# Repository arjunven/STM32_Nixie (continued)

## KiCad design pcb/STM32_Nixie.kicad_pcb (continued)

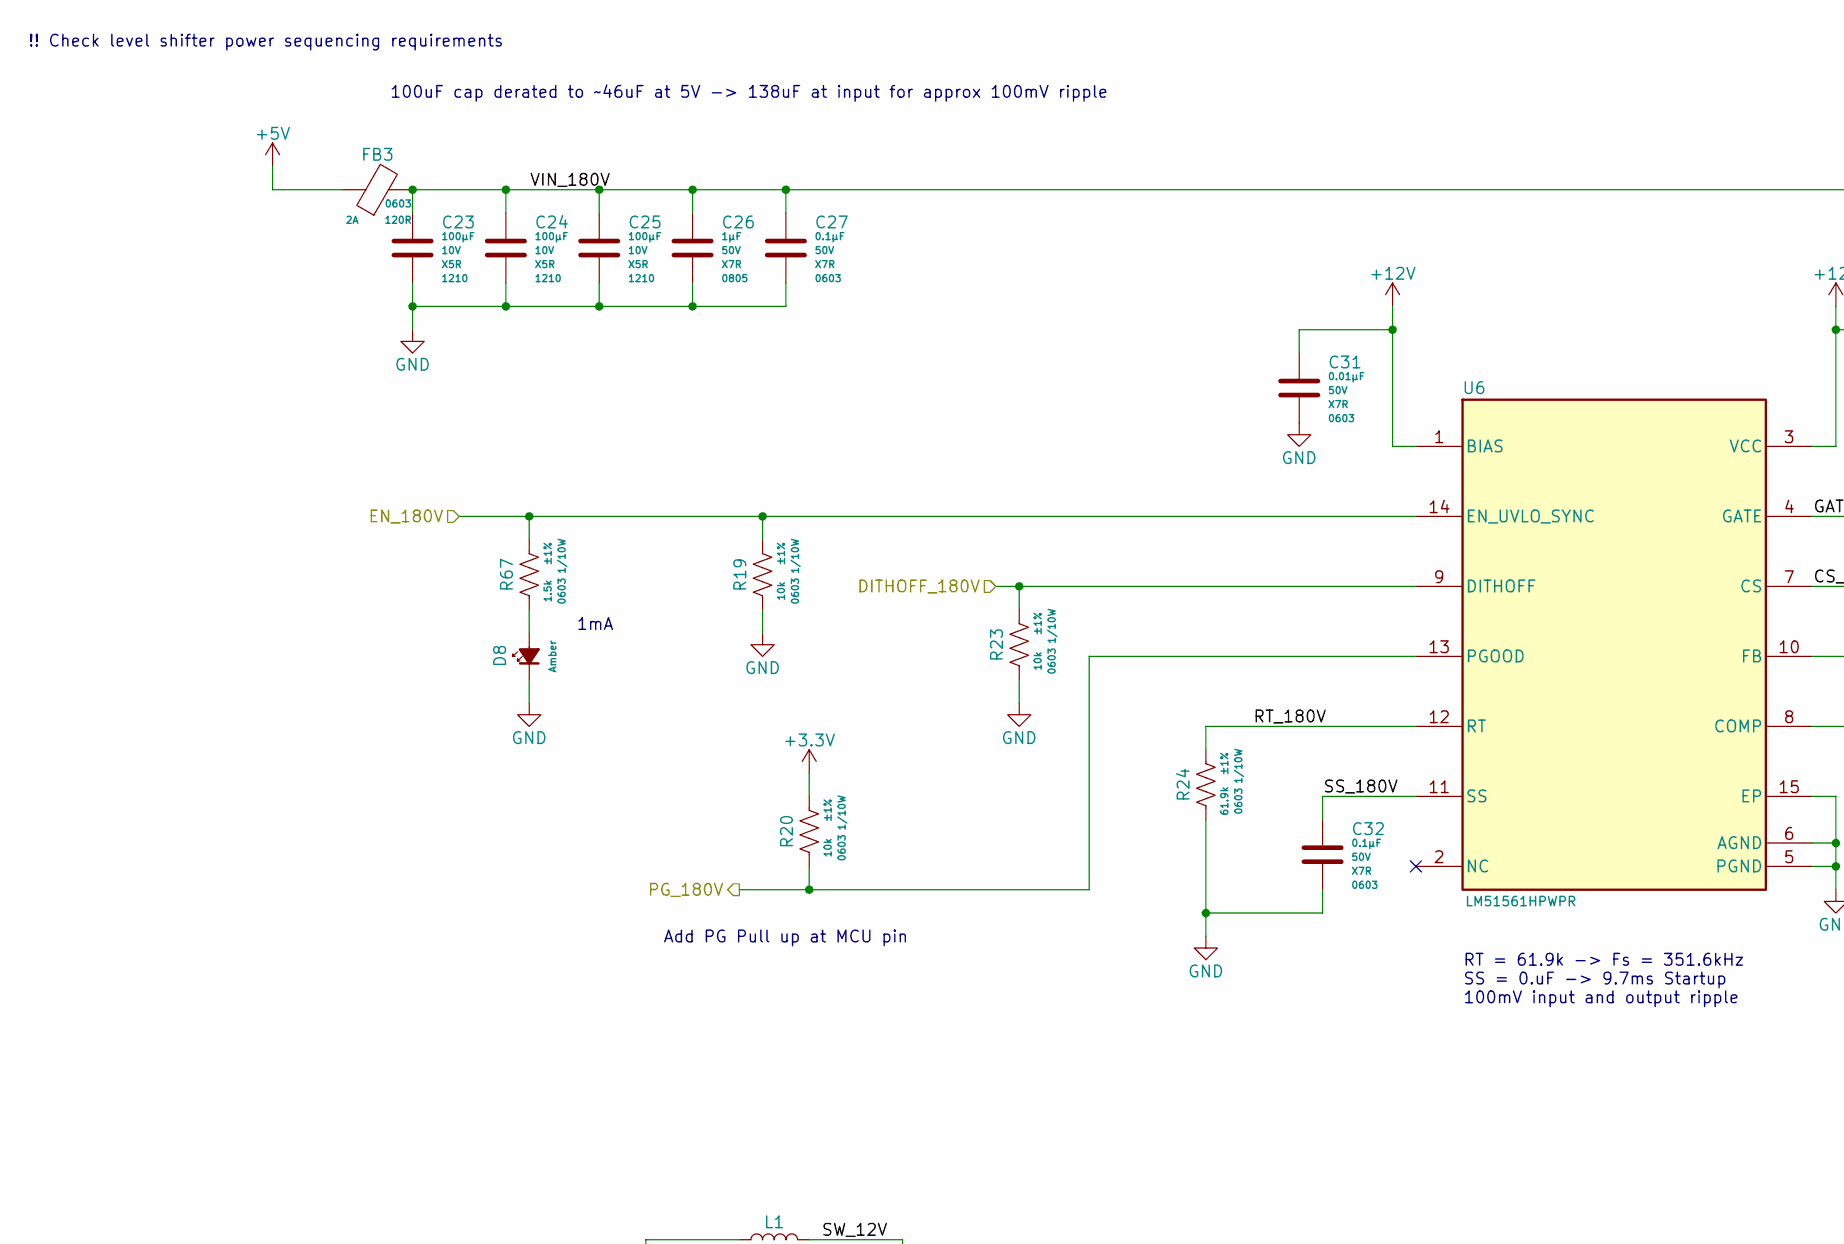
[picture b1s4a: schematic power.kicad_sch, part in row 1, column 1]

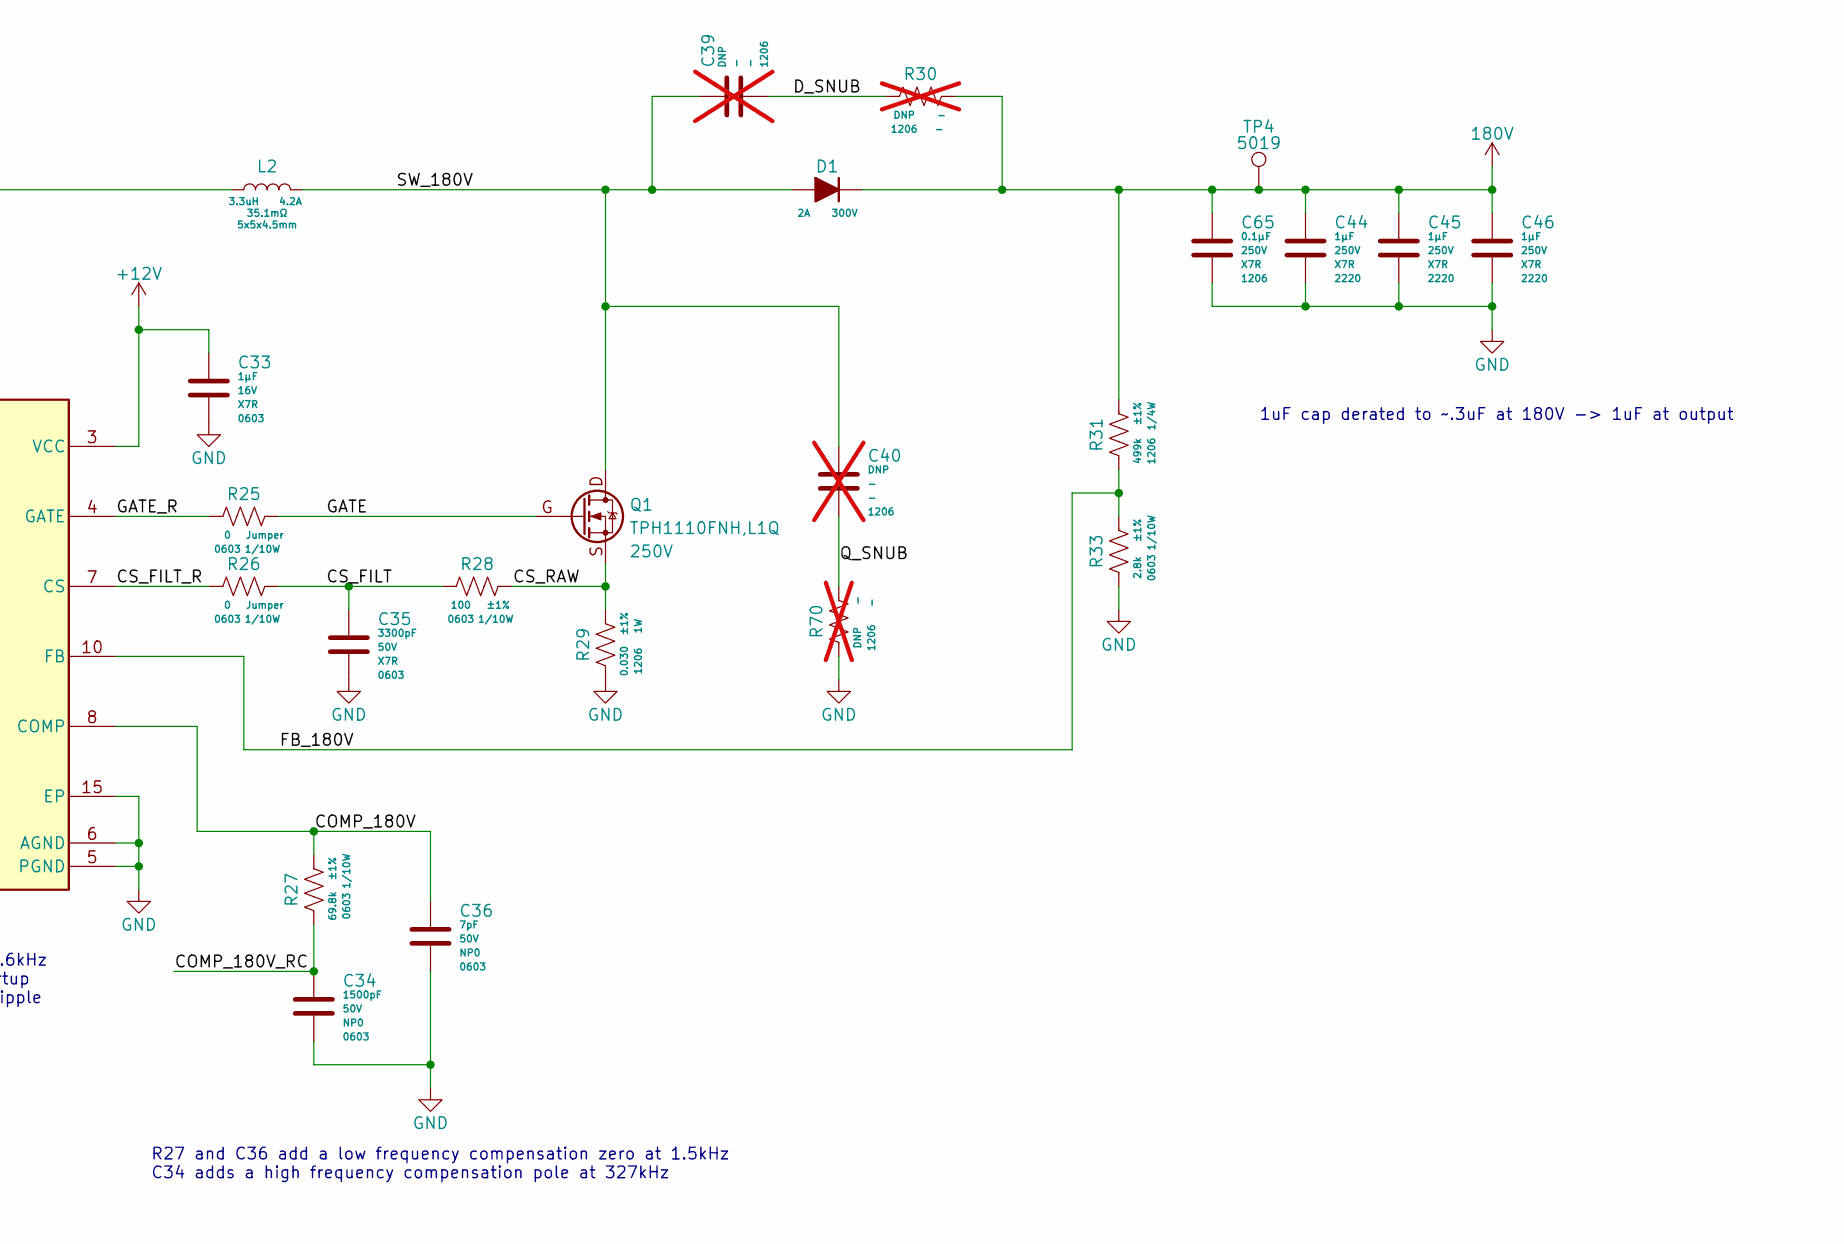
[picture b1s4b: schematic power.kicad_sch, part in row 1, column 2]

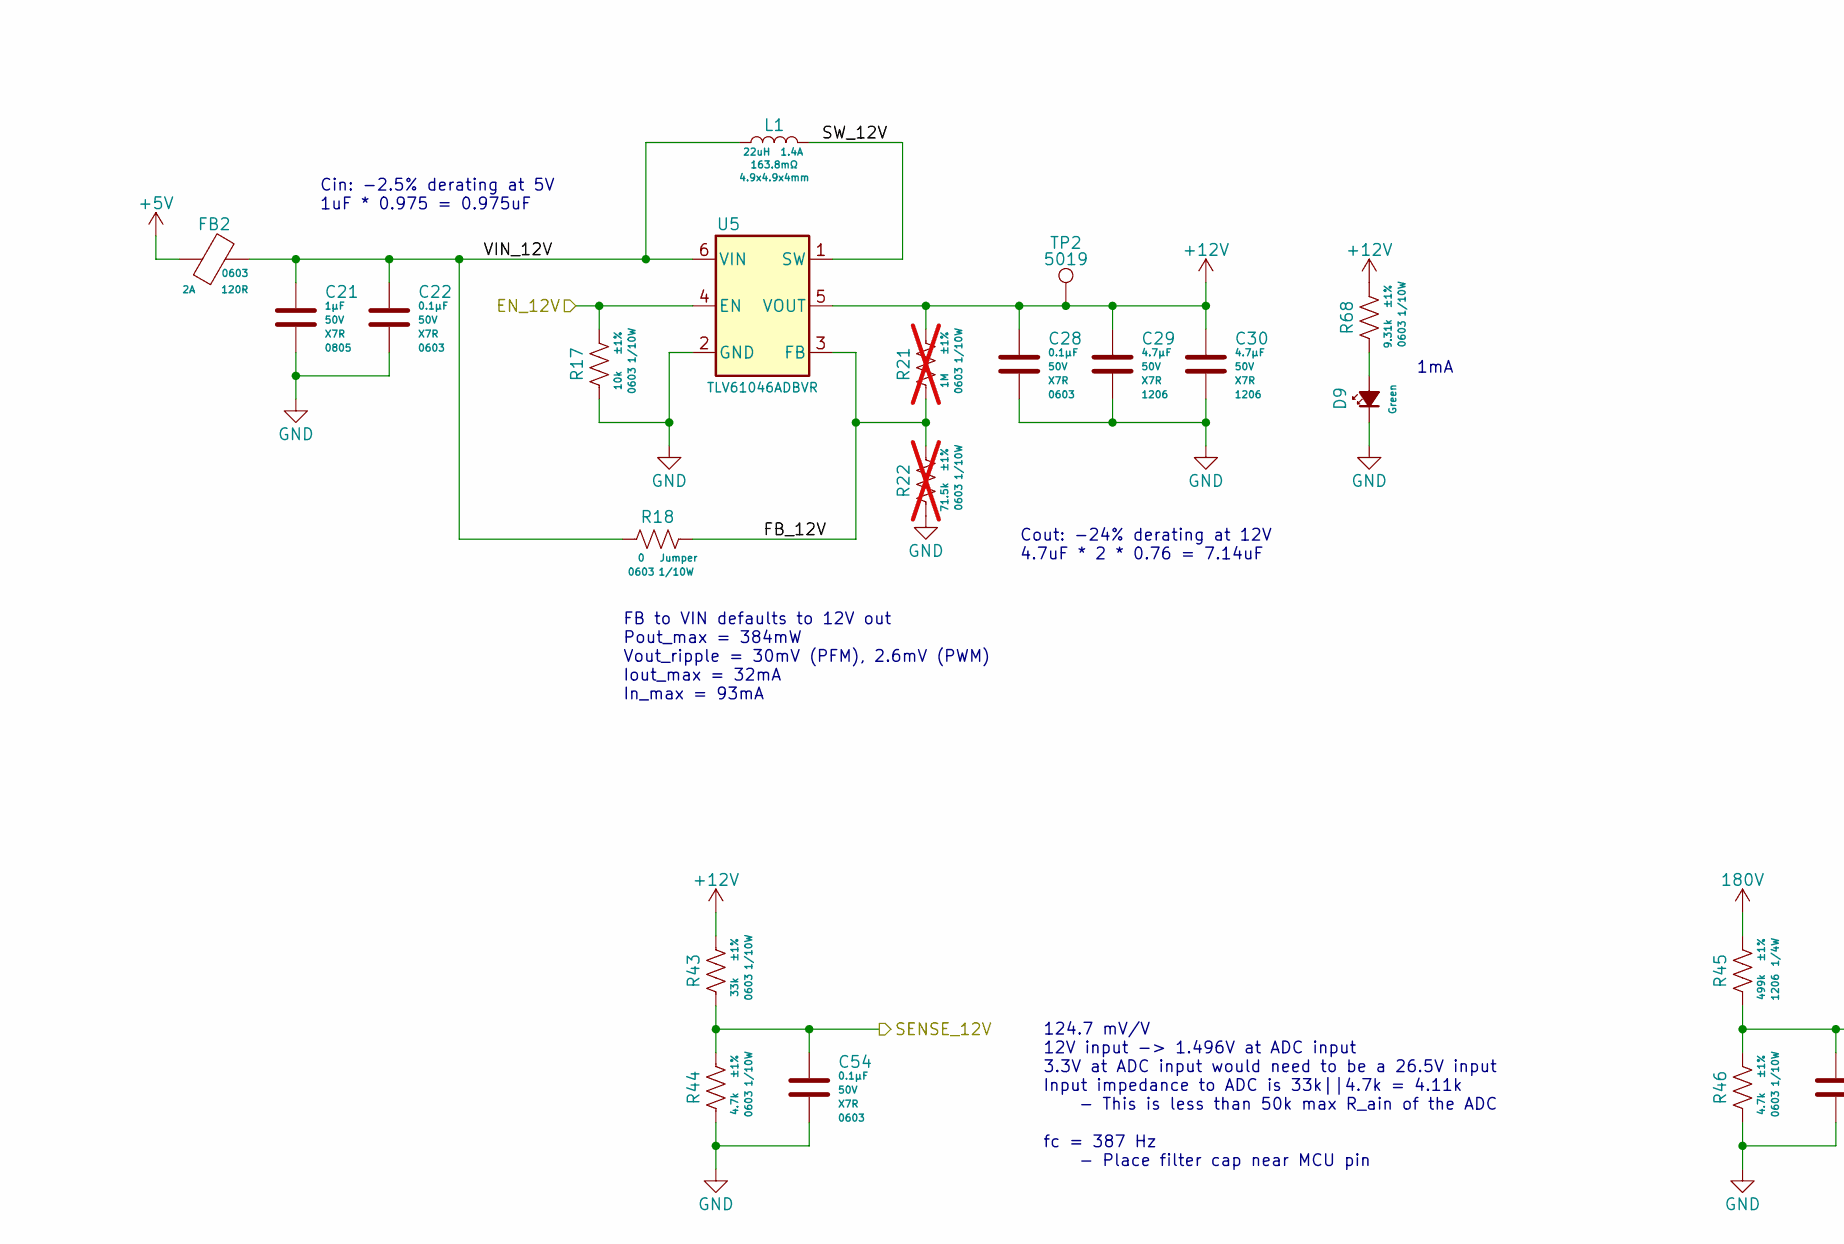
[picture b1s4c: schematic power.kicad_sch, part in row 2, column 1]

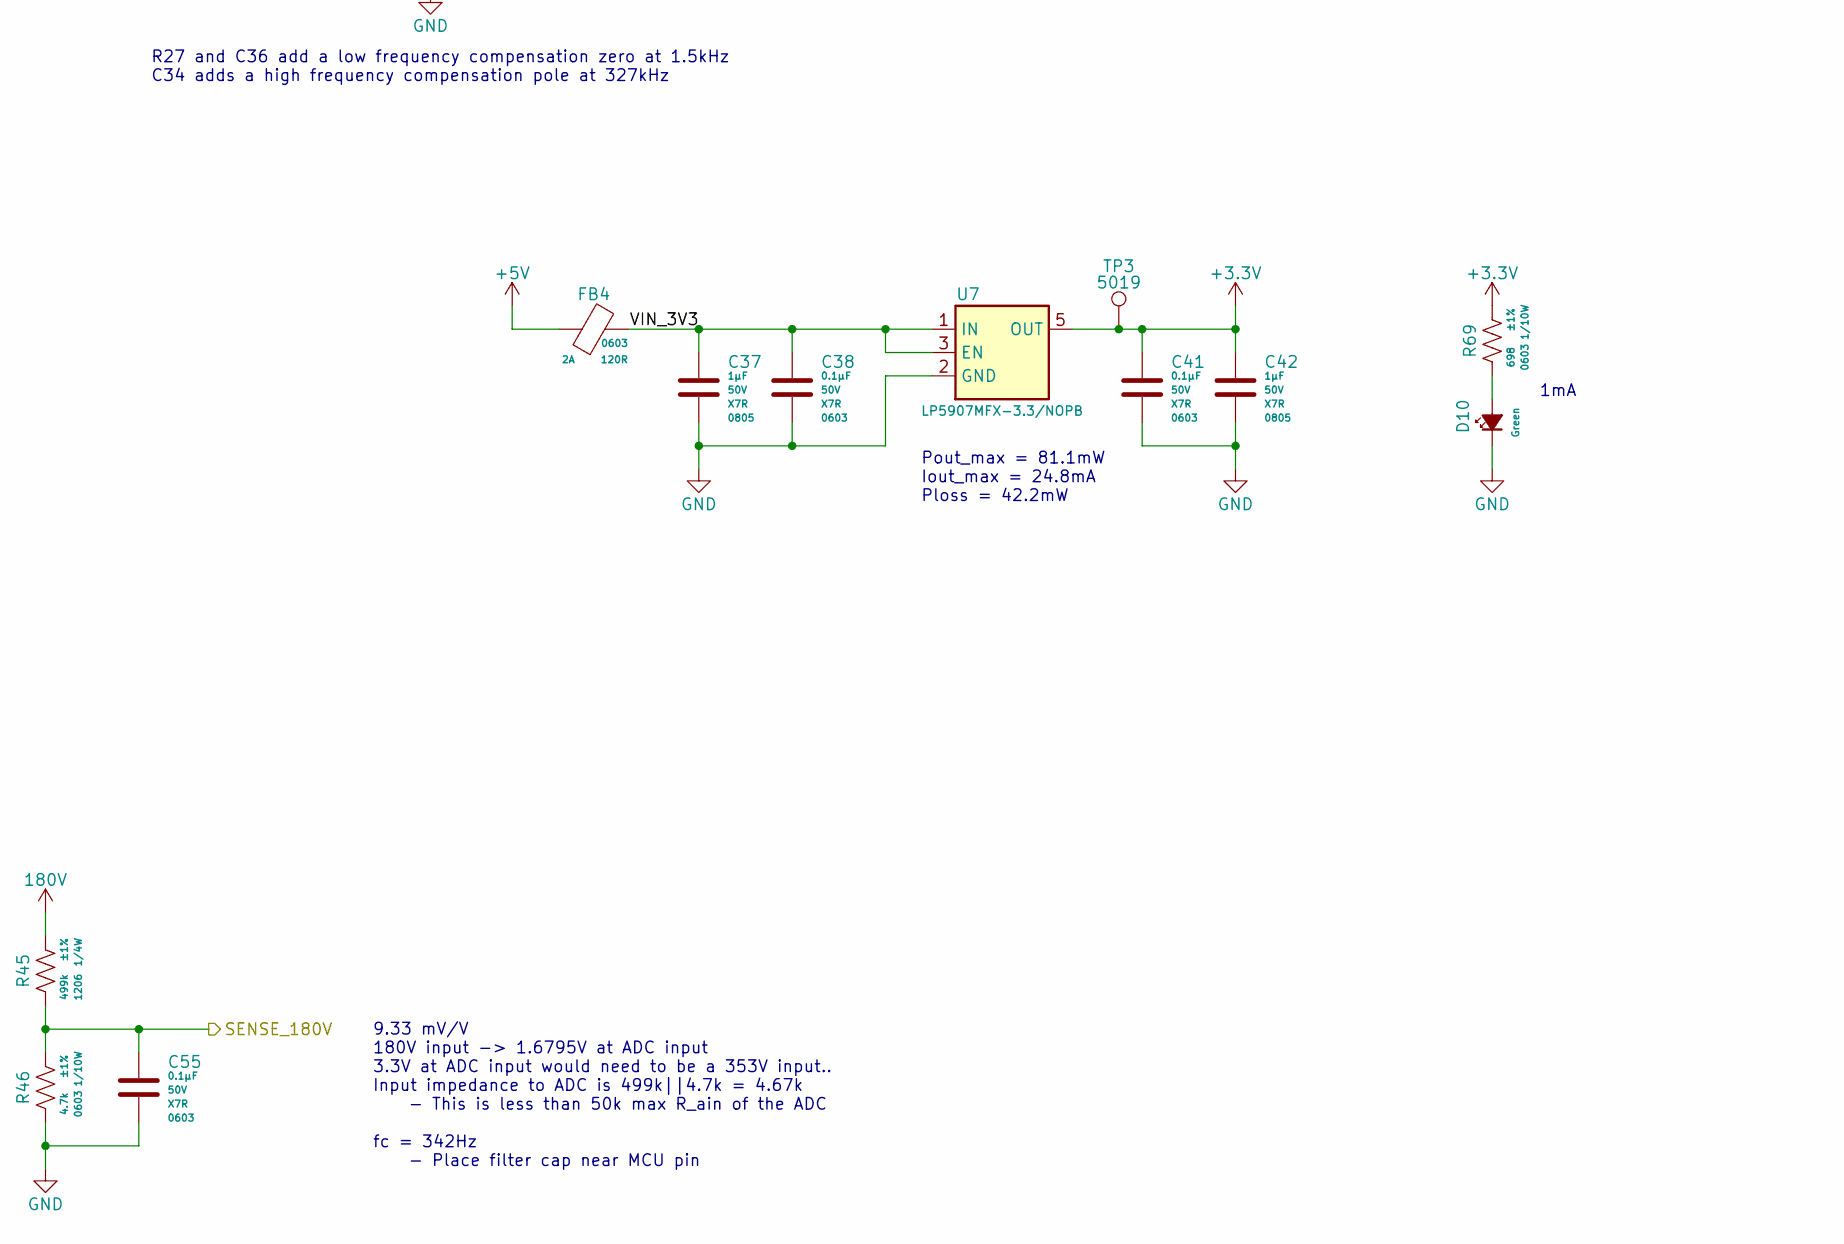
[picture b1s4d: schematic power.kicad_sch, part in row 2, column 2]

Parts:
C21, C26, C37, C42: CAP_CER_1u_50V_X7R_0805; C_0805_2012Metric; Voltage 50V; ManufacturerPN CL21B105KBFNNNE
C22, C27, C28, C32, C38, C41, C54, C55: CAP_CER_0u1_50V_X7R_0603; C_0603_1608Metric; Voltage 50V; ManufacturerPN CL10B104KB8NNNC
C23, C24, C25: CAP_CER_100u_10V_X5R_1210; C_1210_3225Metric; Voltage 10V; ManufacturerPN GRM32ER61A107ME20L
C29, C30: CAP_CER_4u7_50V_X7R_1206; C_1206_3216Metric; Voltage 50V; ManufacturerPN CL31B475KBHNFNE
C31: CAP_CER_0u01_50V_X7R_0603; C_0603_1608Metric; Voltage 50V; ManufacturerPN CL10B103KB8NNNC
C33: CAP_CER_1u_16V_X7R_0603; C_0603_1608Metric; Voltage 16V; ManufacturerPN CC0603KRX7R7BB105
C34: CAP_CER_1500p_50V_NP0_0603; C_0603_1608Metric; Voltage 50V; ManufacturerPN GRM1885C1H152JA01D
C35: CAP_CER_3300p_50V_X7R_0603; C_0603_1608Metric; Voltage 50V; ManufacturerPN CL10B332KB8NNNC
C36: CAP_CER_7p_50V_NP0_0603; C_0603_1608Metric; Voltage 50V; ManufacturerPN CL10C070CB8NNNC
C39, C40: CAP_CER_DNP_1206; C_1206_3216Metric; ManufacturerPN DNP; not fitted
C44, C45, C46: CAP_CER_1u_250V_X7R_2220; C_2220_5750Metric; Voltage 250V; ManufacturerPN C5750X7R2E105K230KA
C65: CAP_CER_0u1_250V_X7R_1206; C_1206_3216Metric; Voltage 250V; ManufacturerPN CL31B104KEHSFNE
D1: D_300V_2A_SMB; D_SMB; ManufacturerPN ES2GHE3_A/H
D8: LED_AMBER_0603; LED_0603_1608Metric; ManufacturerPN 150060AS75000
D9, D10: LED_GREEN_0603; LED_0603_1608Metric; ManufacturerPN 150060GS75000
FB2, FB3, FB4: FER_120R_2A_0603; L_0603_1608Metric; ManufacturerPN BLM18PG121SH1D
L1: IND_22u_1A4_163m8R_4r9x4r9x4; IND_Taiyo-Yuden_NR-50xx; ManufacturerPN NRS5040T220MMGK
L2: IND_3u3_4A2_35m1R_5x5x4r5; IND_VLS5045EX-3R3N; ManufacturerPN VLS5045EX-3R3N
Q1: NFET_250V_10A_TPH1110FNH,L1Q; SOP Advance_TOS; ManufacturerPN TPH1110FNH,L1Q
R17, R19, R20, R23: RES_10K_1P_1/10W_0603; R_0603_1608Metric; Tolerance ±1%; ManufacturerPN RC0603FR-0710KL
R18, R25, R26: RES_0R_1/10W_0603; R_0603_1608Metric; Tolerance Jumper; ManufacturerPN RMCF0603ZT0R00
R21: RES_1M_1P_1/10W_0603; R_0603_1608Metric; Tolerance ±1%; ManufacturerPN RMCF0603FT1M00; not fitted
R22: RES_71K5_1P_1/10W_0603; R_0603_1608Metric; Tolerance ±1%; ManufacturerPN ERJ-3EKF7152V; not fitted
R24: RES_61K9_1P_1/10W_0603; R_0603_1608Metric; Tolerance ±1%; ManufacturerPN ERJ-3EKF6192V
R27: RES_69K8_1P_1/10W_0603; R_0603_1608Metric; Tolerance ±1%; ManufacturerPN RC0603FR-0769K8L
R28: RES_100R_1P_1/10W_0603; R_0603_1608Metric; Tolerance ±1%; ManufacturerPN ERJ-3EKF1000V
R29: RES_R030_1P_1W_1206; R_1206_3216Metric; Tolerance ±1%; ManufacturerPN TLRP2B10DR030FTD
R30, R70: RES_DNP_1206; R_1206_3216Metric; ManufacturerPN DNP; not fitted
R31: RES_499K_1P_1/4W_1206; R_1206_3216Metric; Tolerance ±1%; ManufacturerPN RC1206FR-07499KL
R33: RES_2K8_1P_1/10W_0603; R_0603_1608Metric; Tolerance ±1%; ManufacturerPN RC0603FR-072K8L
R43: RES_33K_1P_1/10W_0603; R_0603_1608Metric; Tolerance ±1%; ManufacturerPN RMCF0603FT33K0
R44, R46: RES_4K7_1P_1/10W_0603; R_0603_1608Metric; Tolerance ±1%; ManufacturerPN RC0603FR-074K7L
R45: RES_499K_1P_1/4W_0805; R_1206_3216Metric; Tolerance ±1%; ManufacturerPN RC1206FR-07499KL
R67: RES_1K5_1P_1/10W_0603; R_0603_1608Metric; Tolerance ±1%; ManufacturerPN RC0603FR-071K5L
R68: RES_9K31_1P_1/10W_0603; R_0603_1608Metric; Tolerance ±1%; ManufacturerPN RC0603FR-079K31L
R69: RES_698R_1P_1/10W_0603; R_0603_1608Metric; Tolerance ±1%; ManufacturerPN RC0603FR-07698RL
TP2: 12V; TestPoint_Keystone_5019_Minature; ManufacturerPN 5019
TP3: 3V3; TestPoint_Keystone_5019_Minature; ManufacturerPN 5019
TP4: 180V; TestPoint_Keystone_5019_Minature; ManufacturerPN 5019
U5: REG_SW_BOOST_TI_TLV61046ADBV; SOT-23-6_TI; ManufacturerPN TLV61046ADBVR
U6: REG_SW_BOOST_TI_LM51561HPWPR; PWP0014H-MFG; ManufacturerPN LM51561HPWPR
U7: REG_LDO_3V3_250mA_TI_LP5907MFX-3.3; SOT-23-5_TI; ManufacturerPN LP5907MFX-3.3/NOPB

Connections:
180V: C44.1, C45.1, C46.1, C65.1, D1.1 (K), R30.1, R31.1, R45.1, TP4.1; also elsewhere on the board
+3.3V: C41.1, C42.1, R20.1, R69.1, TP3.1, U7.5 (OUT); also elsewhere on the board
+5V: FB2.1, FB3.1, FB4.1; also elsewhere on the board
+12V: C28.1, C29.1, C30.1, C31.1, C33.1, R21.1, R43.1, R68.1, TP2.1, U5.5 (VOUT), U6.1 (BIAS), U6.3 (VCC); also elsewhere on the board
/MCU/DITHOFF_180V: R23.1, U6.9 (DITHOFF); also elsewhere on the board
/MCU/EN_12V: R17.1, U5.4 (EN); also elsewhere on the board
/MCU/EN_180V: R19.1, R67.1, U6.14 (EN_UVLO_SYNC); also elsewhere on the board
/MCU/PG_180V: R20.2, U6.13 (PGOOD); also elsewhere on the board
/MCU/SENSE_12V: C54.1, R43.2, R44.1; also elsewhere on the board
/MCU/SENSE_180V: C55.1, R45.2, R46.1; also elsewhere on the board
/Power/COMP_180V: C36.1, R27.1, U6.8 (COMP)
/Power/COMP_180V_RC: C34.1, R27.2
/Power/CS_FILT: C35.1, R26.1, R28.2
/Power/CS_FILT_R: R26.2, U6.7 (CS)
/Power/CS_RAW: Q1.S, R28.1, R29.1
/Power/D_SNUB: C39.2, R30.2
/Power/FB_12V: R18.1, R21.2, R22.1, U5.3 (FB)
/Power/FB_180V: R31.2, R33.1, U6.10 (FB)
/Power/GATE: Q1.G, R25.1
/Power/GATE_R: R25.2, U6.4 (GATE)
/Power/Q_SNUB: C40.2, R70.1
/Power/RT_180V: R24.1, U6.12 (RT)
/Power/SS_180V: C32.1, U6.11 (SS)
/Power/SW_12V: L1.2, U5.1 (SW)
/Power/SW_180V: C39.1, C40.1, D1.2 (A), L2.2, Q1.D
/Power/VIN_3V3: C37.1, C38.1, FB4.2, U7.1 (IN), U7.3 (EN)
/Power/VIN_12V: C21.1, C22.1, FB2.2, L1.1, R18.2, U5.6 (VIN)
/Power/VIN_180V: C23.1, C24.1, C25.1, C26.1, C27.1, FB3.2, L2.1
GND: C21.2, C22.2, C23.2, C24.2, C25.2, C26.2, C27.2, C28.2, C29.2, C30.2, C31.2, C32.2, C33.2, C34.2, C35.2, C36.2, C37.2, C38.2, C41.2, C42.2, C44.2, C45.2, C46.2, C54.2, C55.2, C65.2, D8.1 (K), D9.1 (K), D10.1 (K), R17.2, R19.2, R22.2, R23.2, R24.2, R29.2, R33.2, R44.2, R46.2, R70.2, U5.2 (GND), U6.5 (PGND), U6.6 (AGND), U6.15 (EP), U7.2 (GND); also elsewhere on the board
unnamed: D8.2 (A), R67.2
unnamed: D9.2 (A), R68.2
unnamed: D10.2 (A), R69.2

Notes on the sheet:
!! Check level shifter power sequencing requirements
FB to VIN defaults to 12V out Pout_max = 384mW Vout_ripple = 30mV (PFM), 2.6mV (PWM) Iout_max = 32mA In_max = 93mA
9.33 mV/V 180V input -> 1.6795V at ADC input 3.3V at ADC input would need to be a 353V input.. Input impedance to ADC is 499k||4.7k = 4.67k - This is less than 50k max R_ain of the ADC fc = 342Hz - Place filter cap near MCU pin
1mA
124.7 mV/V 12V input -> 1.496V at ADC input 3.3V at ADC input would need to be a 26.5V input Input impedance to ADC is 33k||4.7k = 4.11k - This is less than 50k max R_ain of the ADC fc = 387 Hz - Place filter cap near MCU pin
Cout: -24% derating at 12V 4.7uF * 2 * 0.76 = 7.14uF
R27 and C36 add a low frequency compensation zero at 1.5kHz C34 adds a high frequency compensation pole at 327kHz
100uF cap derated to ~46uF at 5V -> 138uF at input for approx 100mV ripple
Add PG Pull up at MCU pin
1uF cap derated to ~.3uF at 180V -> 1uF at output
RT = 61.9k -> Fs = 351.6kHz SS = 0.uF -> 9.7ms Startup 100mV input and output ripple
Pout_max = 81.1mW Iout_max = 24.8mA Ploss = 42.2mW
Cin: -2.5% derating at 5V 1uF * 0.975 = 0.975uF

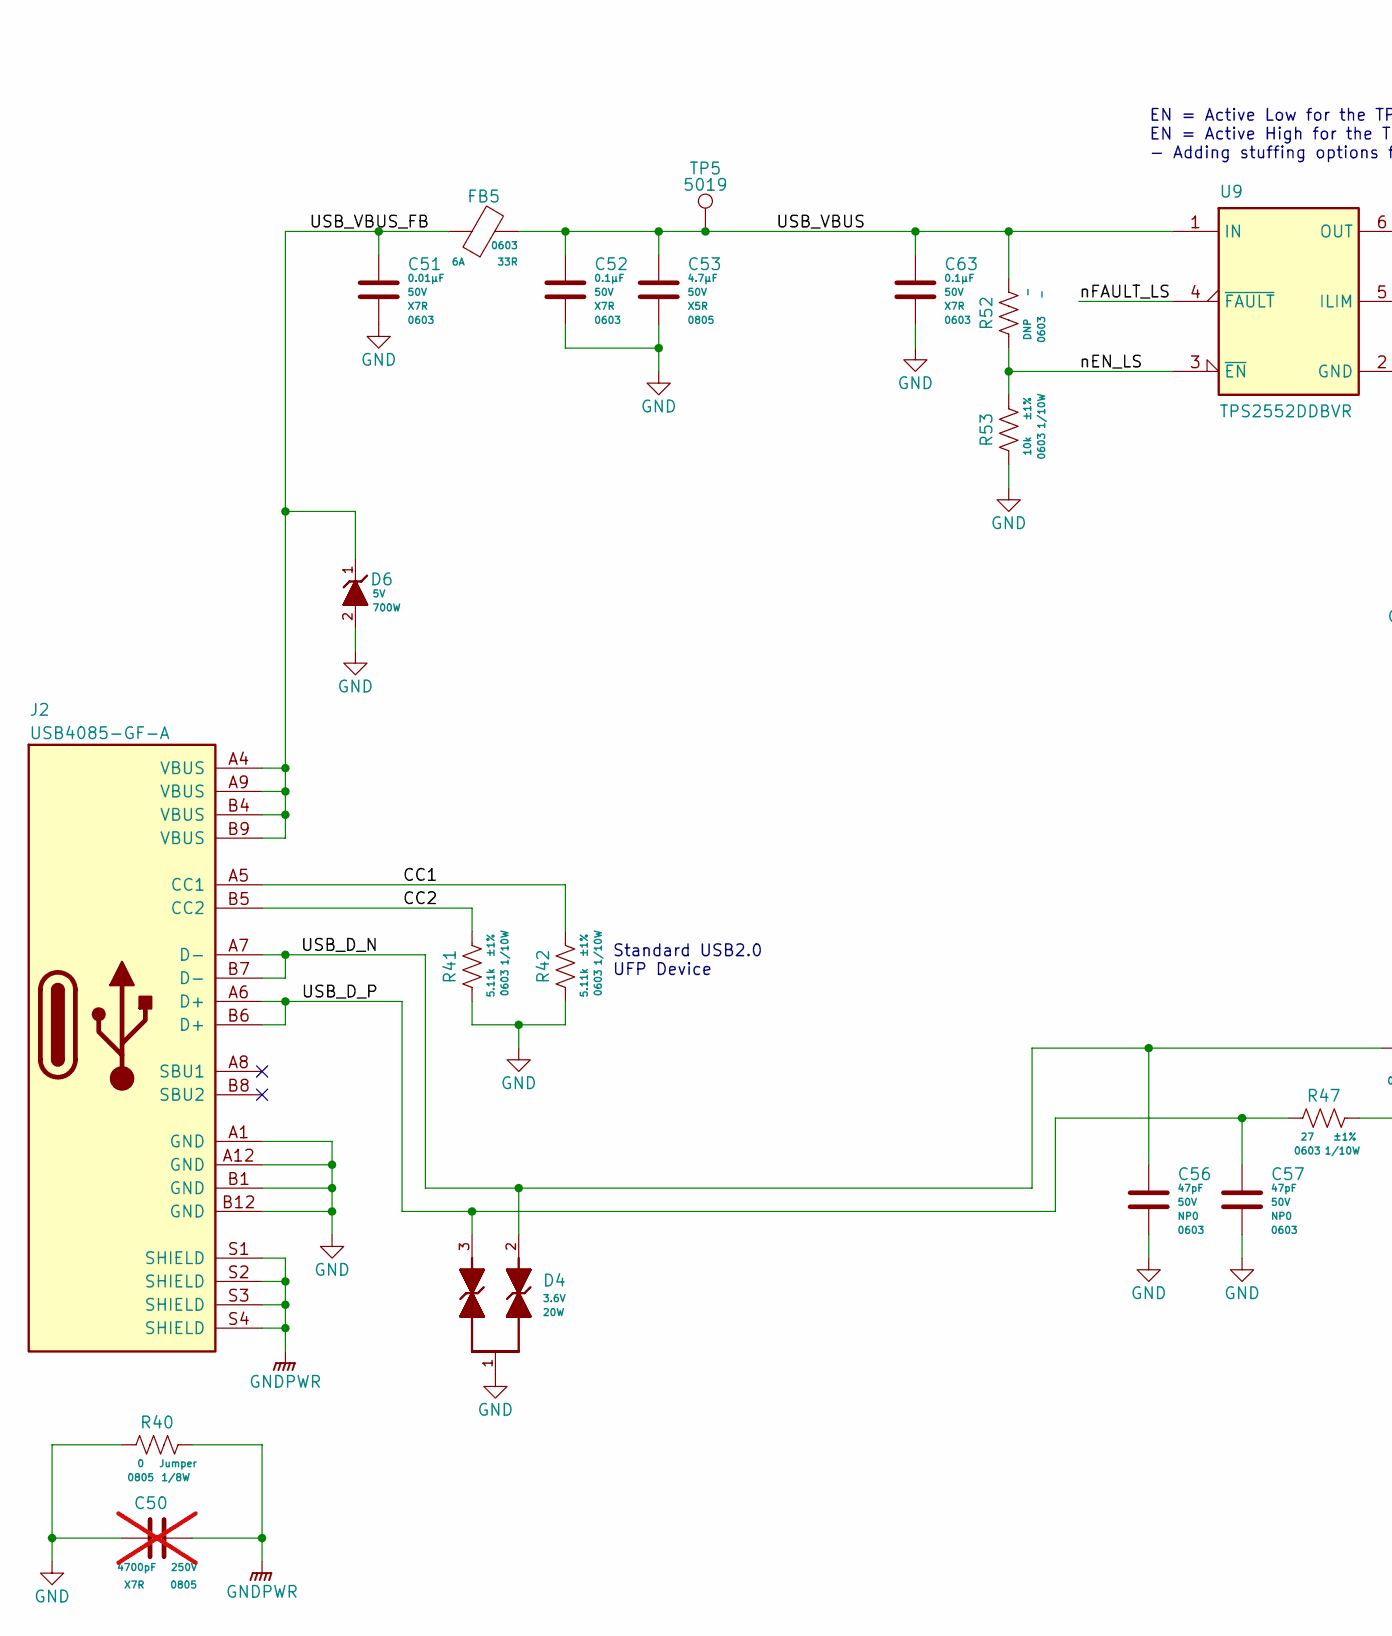
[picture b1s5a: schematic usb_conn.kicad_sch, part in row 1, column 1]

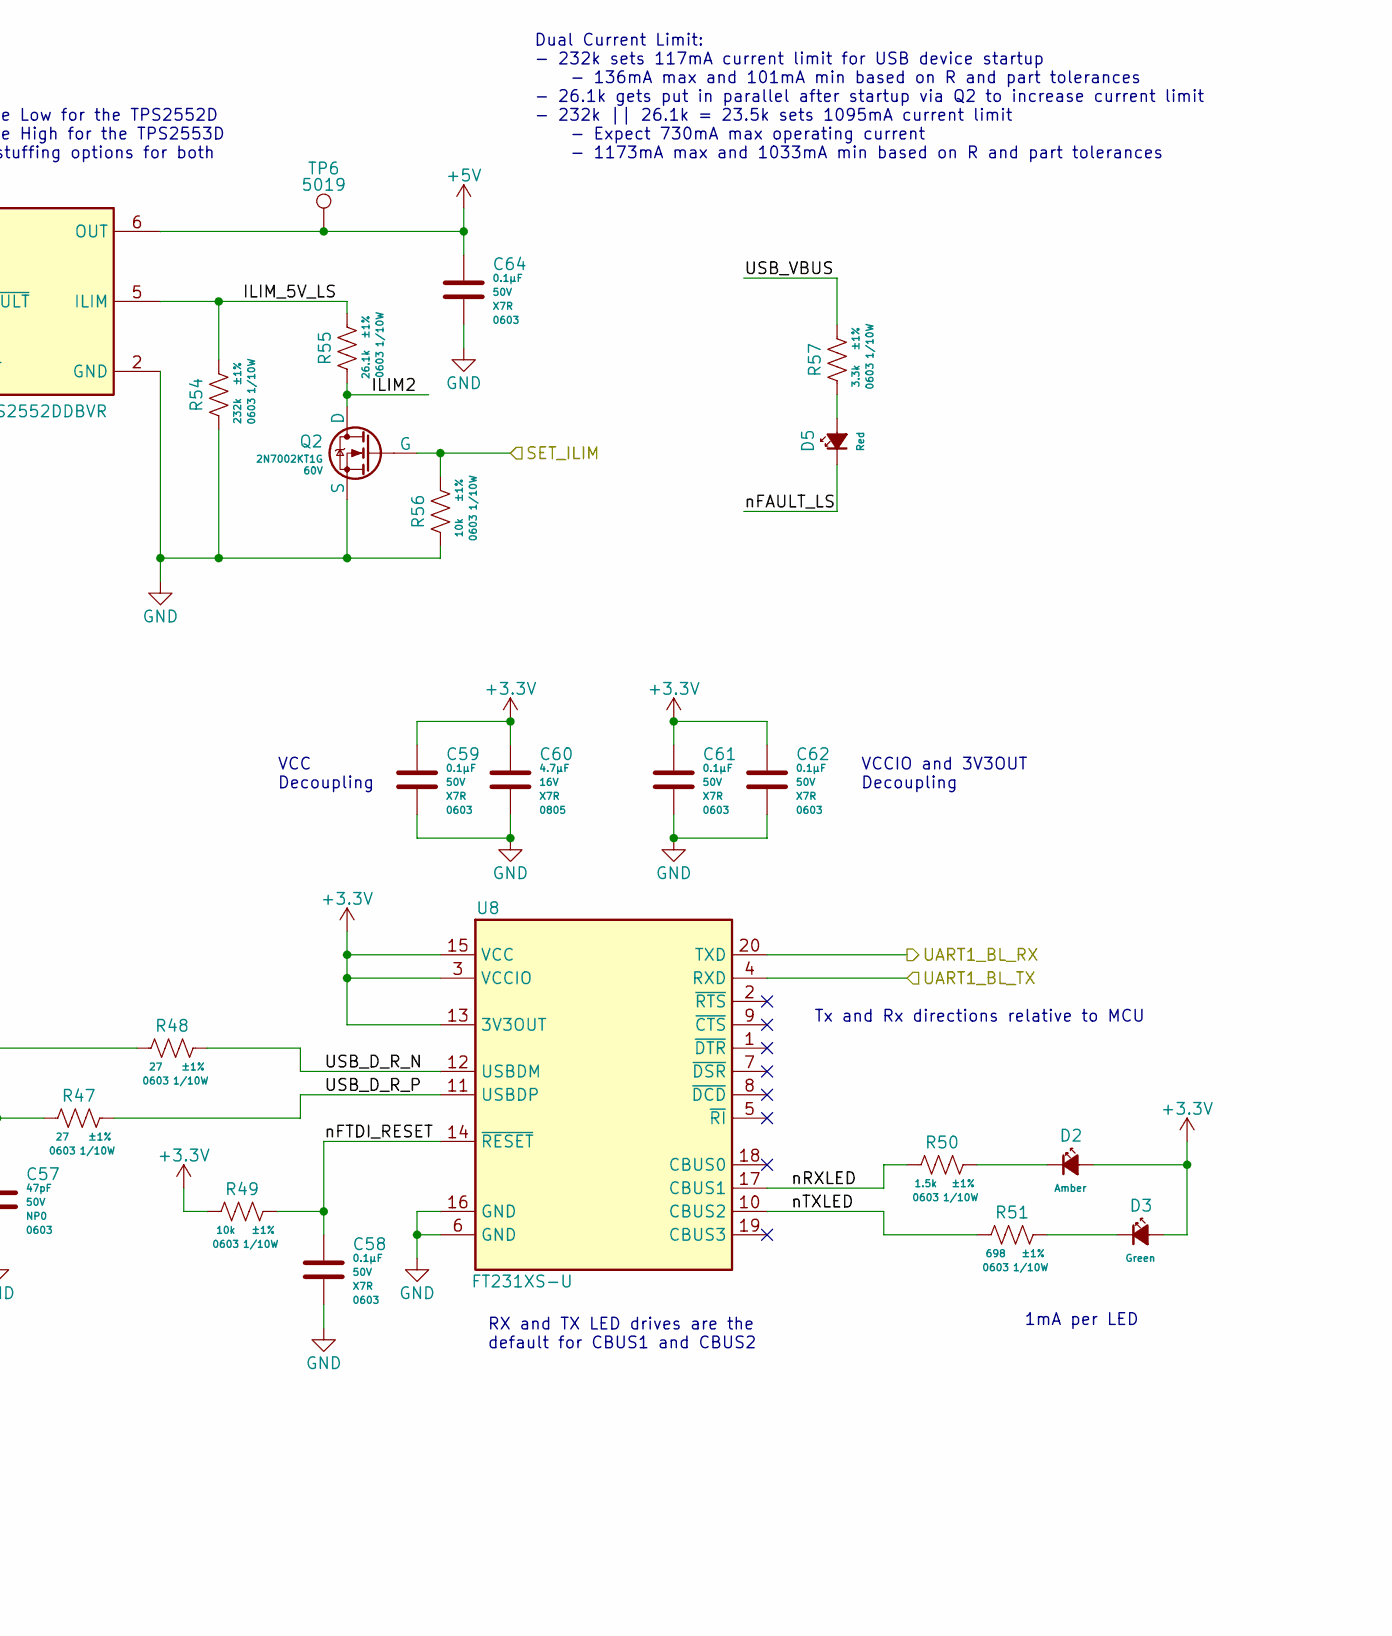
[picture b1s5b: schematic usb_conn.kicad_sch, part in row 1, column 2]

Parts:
C50: CAP_CER_4700p_250V_X7R_0805; C_0805_2012Metric; Voltage 250V; ManufacturerPN CC0805KRX7RYBB472; not fitted
C51: CAP_CER_0u01_50V_X7R_0603; C_0603_1608Metric; Voltage 50V; ManufacturerPN CL10B103KB8NNNC
C52, C58, C59, C61, C62, C63, C64: CAP_CER_0u1_50V_X7R_0603; C_0603_1608Metric; Voltage 50V; ManufacturerPN CL10B104KB8NNNC
C53: CAP_CER_4u7_50V_X5R_0805; C_0805_2012Metric; Voltage 50V; ManufacturerPN GRM21BR61H475KE51L
C56, C57: CAP_CER_47p_50V_NP0_0603; C_0603_1608Metric; Voltage 50V; ManufacturerPN CL10C470JB8NNNC
C60: CAP_CER_4u7_16V_X7R_0805; C_0805_2012Metric; Voltage 16V; ManufacturerPN GRM21BR71C475KE51L
D2: LED_AMBER_0603; LED_0603_1608Metric; ManufacturerPN 150060AS75000
D3: LED_GREEN_0603; LED_0603_1608Metric; ManufacturerPN 150060GS75000
D4: D_TVS_BI_3V6_20W_3-XFDFN; DIO_ESD122DMYR; ManufacturerPN ESD122DMYR
D5: LED_RED_0603; LED_0603_1608Metric; ManufacturerPN 150060RS75000
D6: D_TVS_UNI_5V_700W_2-UDFN; QFN-2L_STM; ManufacturerPN ESDA7P60-1U1M
FB5: FER_33R_6A_0603; L_0603_1608Metric; ManufacturerPN BLM18SG330SN1D
J2: CONN_USBC_RCPT_USB2.0_USB4085-GF-A; GCT_USB4085-GF-A_REVA4; ManufacturerPN USB4085-GF-A
Q2: NFET_60V_0A5_2N7002KT1G; SOT-23_ONSEMI; ManufacturerPN 2N7002KT1G
R40: RES_0R_1/8W_0805; R_0805_2012Metric; Tolerance Jumper; ManufacturerPN RMCF0805ZT0R00
R41, R42: RES_5K11_1P_1/10W_0603; R_0603_1608Metric; Tolerance ±1%; ManufacturerPN CRCW06035K11FKEAC
R47, R48: RES_27R_1P_1/10W_0603; R_0603_1608Metric; Tolerance ±1%; ManufacturerPN RC0603JR-0727RL
R49, R53, R56: RES_10K_1P_1/10W_0603; R_0603_1608Metric; Tolerance ±1%; ManufacturerPN RC0603FR-0710KL
R50: RES_1K5_1P_1/10W_0603; R_0603_1608Metric; Tolerance ±1%; ManufacturerPN RC0603FR-071K5L
R51: RES_698R_1P_1/10W_0603; R_0603_1608Metric; Tolerance ±1%; ManufacturerPN RC0603FR-07698RL
R52: RES_DNP_0603; R_0603_1608Metric; ManufacturerPN DNP
R54: RES_232K_1P_1/10W_0603; R_0603_1608Metric; Tolerance ±1%; ManufacturerPN RC0603FR-07232KL
R55: RES_26K1_1P_1/10W_0603; R_0603_1608Metric; Tolerance ±1%; ManufacturerPN RC0603FR-0726K1L
R57: RES_3K3_1P_1/10W_0603; R_0603_1608Metric; Tolerance ±1%; ManufacturerPN RMCF0603FT3K30
TP5: VBUS; TestPoint_Keystone_5019_Minature; ManufacturerPN 5019
TP6: 5V; TestPoint_Keystone_5019_Minature; ManufacturerPN 5019
U8: IC_FTDI_FT231XS; SSOP-20_3.9x8.7mm_P0.635mm; ManufacturerPN FT231XS-U
U9: IC_LSW_TI_TPS2552D; SOT-23-6_TI; ManufacturerPN TPS2552DDBVR

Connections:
+3.3V: C59.1, C60.1, C61.1, C62.1, D2.2 (A), D3.2 (A), R49.2, U8.3 (VCCIO), U8.13 (3V3OUT), U8.15 (VCC); also elsewhere on the board
+5V: C64.1, TP6.1, U9.6 (OUT); also elsewhere on the board
/MCU/SET_ILIM: Q2.1 (G), R56.1; also elsewhere on the board
/MCU/UART1_BL_RX: U8.20 (TXD); also elsewhere on the board
/MCU/UART1_BL_TX: U8.4 (RXD); also elsewhere on the board
/USB Connector/CC1: J2.A5 (CC1), R42.1
/USB Connector/CC2: J2.B5 (CC2), R41.1
/USB Connector/ILIM2: Q2.3 (D), R55.2
/USB Connector/ILIM_5V_LS: R54.1, R55.1, U9.5 (ILIM)
/USB Connector/USB_D_N: C56.1, D4.2, J2.A7 (D-), J2.B7 (D-), R48.2
/USB Connector/USB_D_P: C57.1, D4.3, J2.A6 (D+), J2.B6 (D+), R47.2
/USB Connector/USB_D_R_N: R48.1, U8.12 (USBDM)
/USB Connector/USB_D_R_P: R47.1, U8.11 (USBDP)
/USB Connector/USB_VBUS: C52.1, C53.1, C63.1, FB5.2, R52.1, R57.1, TP5.1, U9.1 (IN)
/USB Connector/USB_VBUS_FB: C51.1, D6.1 (K), FB5.1, J2.A4 (VBUS), J2.A9 (VBUS), J2.B4 (VBUS), J2.B9 (VBUS)
/USB Connector/nEN_LS: R52.2, R53.1, U9.3 (~EN)
/USB Connector/nFAULT_LS: D5.1 (K), U9.4 (~FAULT)
/USB Connector/nFTDI_RESET: C58.1, R49.1, U8.14 (~RESET)
/USB Connector/nRXLED: R50.2, U8.17 (CBUS1)
/USB Connector/nTXLED: R51.2, U8.10 (CBUS2)
GND: C50.1, C51.2, C52.2, C53.2, C56.2, C57.2, C58.2, C59.2, C60.2, C61.2, C62.2, C63.2, C64.2, D4.1, D6.2 (A), J2.A1 (GND), J2.A12 (GND), J2.B1 (GND), J2.B12 (GND), Q2.2 (S), R40.2, R41.2, R42.2, R53.2, R54.2, R56.2, U8.6 (GND), U8.16 (GND), U9.2 (GND); also elsewhere on the board
GNDPWR: C50.2, J2.S1 (SHIELD), J2.S2 (SHIELD), J2.S3 (SHIELD), J2.S4 (SHIELD), R40.1
unnamed: D2.1 (K), R50.1
unnamed: D3.1 (K), R51.1
unnamed: D5.2 (A), R57.2

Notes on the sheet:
VCC Decoupling
RX and TX LED drives are the default for CBUS1 and CBUS2
EN = Active Low for the TPS2552D EN = Active High for the TPS2553D - Adding stuffing options for both
Standard USB2.0 UFP Device
Dual Current Limit: - 232k sets 117mA current limit for USB device startup - 136mA max and 101mA min based on R and part tolerances - 26.1k gets put in parallel after startup via Q2 to increase current limit - 232k || 26.1k = 23.5k sets 1095mA current limit - Expect 730mA max operating current - 11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
VCCIO and 3V3OUT Decoupling
Tx and Rx directions relative to MCU
1mA per LED
